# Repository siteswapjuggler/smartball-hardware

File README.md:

# Smartball project - hardware 

This repository contains the Smartball project hardware files: bom, schematics, board layout and 3D printed part.

## Open Source

All the technological development work made in the Smartball project is available under open source licenses. As we don't know yet about how we will deal with further development all of our hardwares will be published under Creative Commons BY-NC-SA and all of our softwares will be under GPL v3.

|Applying to|Licence|Logo|
|---|---|---|
|hardware|[Creatives Commons BY-NC-SA](http://creativecommons.org/licenses/by-nc-sa/4.0/)|[ ](http://creativecommons.org/licenses/by-nc-sa/4.0/)|
|software|[GPL v3](http://www.gnu.org/licenses/gpl.html)||

## Different boards

The project is an assembly of three boards: 2 led boards + 1 main board. It relies on the ESP-12F espressif breakout but could be used with ESP-12E or ESP-12F without any problem.

## Version history

v1.1 is the version product for the first prototypes and contains an minor error on USB Data Lines
v1.2 is the latest version, it correct the USB Data Lines error

## Linked repositories

This repository refers directly to its following siblings : 

- https://github.com/siteswapjuggler/smartball-firmware
- https://github.com/siteswapjuggler/smartball-externals
- https://github.com/siteswapjuggler/smartball-documents
- https://github.com/siteswapjuggler/smartball-imu

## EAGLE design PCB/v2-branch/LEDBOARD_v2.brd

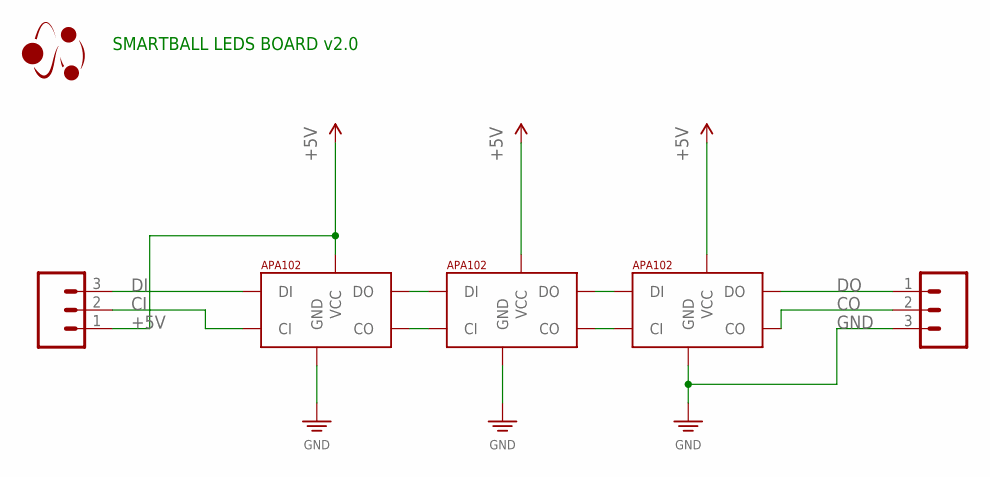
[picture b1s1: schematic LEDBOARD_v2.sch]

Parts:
L1, L2, L3: APA102; APA102_5050_SB
U$4: LOGO_SMARTBALL; SMARTBALL_LOGO
U$5, U$6: CONN_03_SMD_MALECONN03_SMD_MALE; CONN03_SMD_MALE

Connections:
+5V: L1.4 (VCC), L2.4 (VCC), L3.4 (VCC), U$5.1
CI: L1.2 (CI), L1.CI2 (CI), U$5.2
CO: L3.5 (CO), U$6.2
DI: L1.1 (DI), L1.DI2 (DI), U$5.3
DO: L3.6 (DO), U$6.1
GND: L1.3 (GND), L1.GND2 (GND), L2.3 (GND), L2.GND2 (GND), L3.3 (GND), L3.GND2 (GND), U$6.3
unnamed: L1.6 (DO), L2.1 (DI), L2.DI2 (DI)
unnamed: L1.5 (CO), L2.2 (CI), L2.CI2 (CI)
unnamed: L2.6 (DO), L3.1 (DI), L3.DI2 (DI)
unnamed: L2.5 (CO), L3.2 (CI), L3.CI2 (CI)

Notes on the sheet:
SMARTBALL LEDS BOARD v2.0

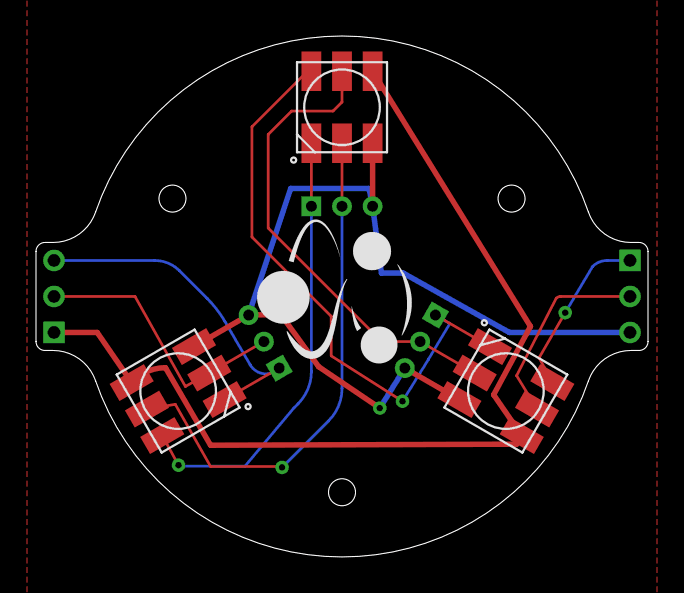
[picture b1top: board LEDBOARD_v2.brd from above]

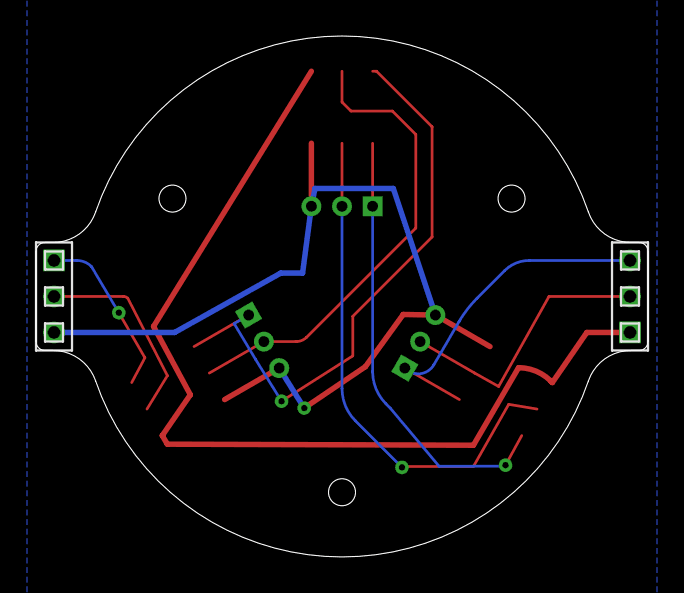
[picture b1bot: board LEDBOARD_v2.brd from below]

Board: 2 copper layers, 34.0 x 28.9 mm, 6 parts (2 on the bottom side), 10 nets.

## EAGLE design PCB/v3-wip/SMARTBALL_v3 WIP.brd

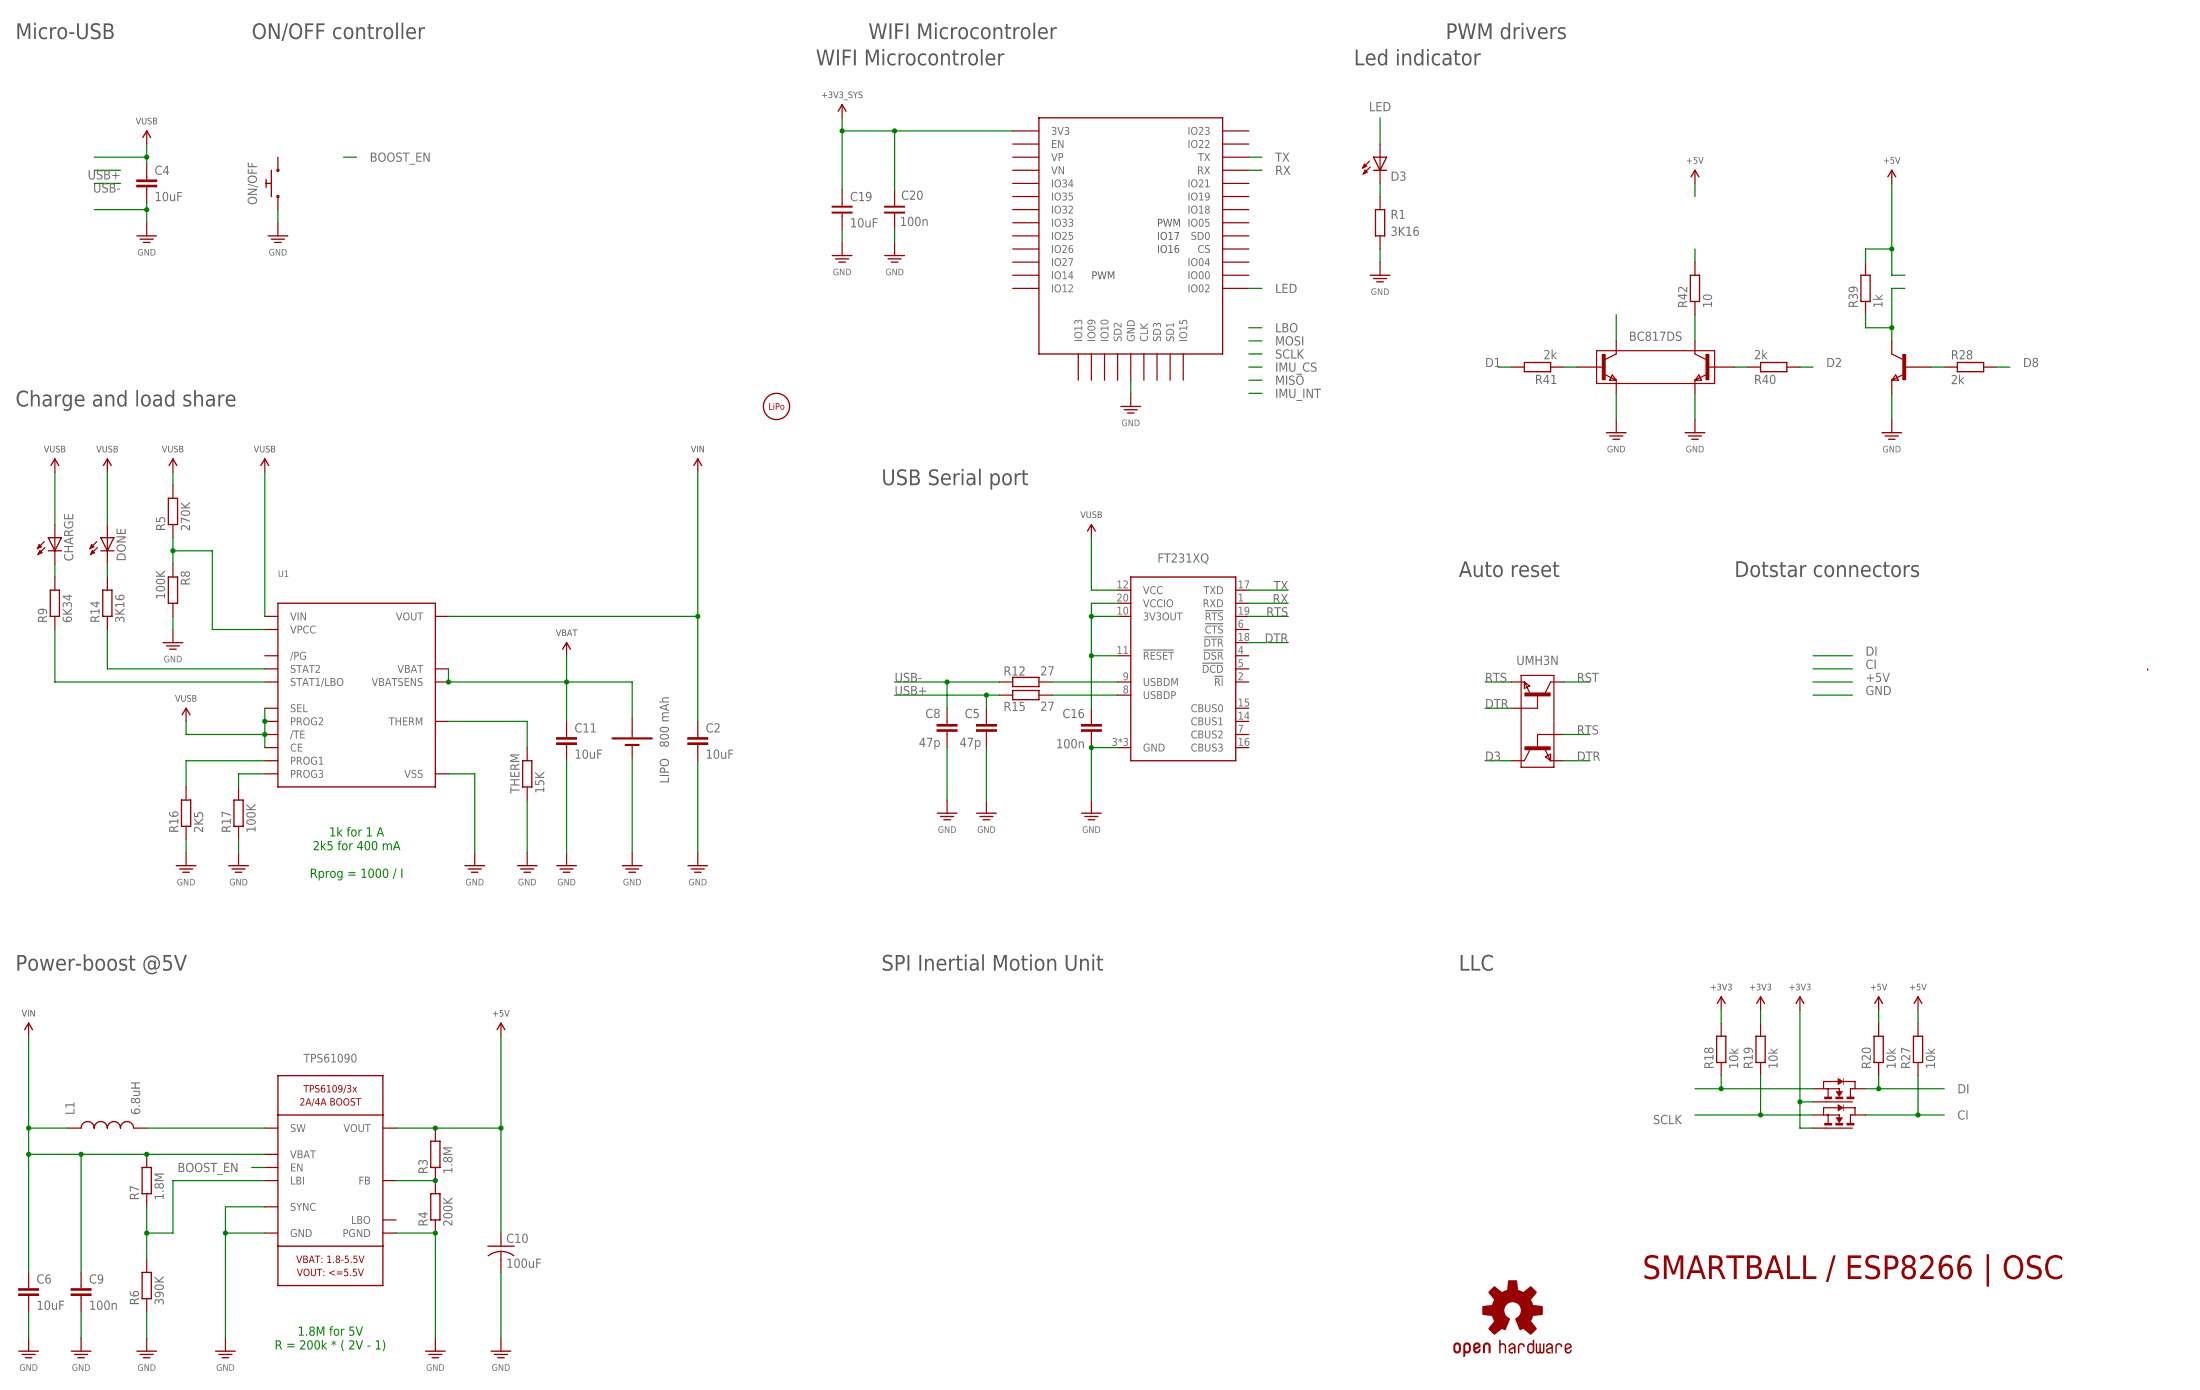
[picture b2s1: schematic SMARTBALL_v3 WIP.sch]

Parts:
BC817DS: SOT_BC817DS; SOT457R_PHILIPS
C2, C4, C6, C11, C19: 10uF; C0603
C5, C8: 47p; C0603
C9, C16, C20: 100n; C0603
C10: 100uF; C1210
CHARGE: LED_KINGBRIGHT_16X08
D3: Blue; LED_KINGBRIGHT_16X08
DONE: LED_KINGBRIGHT_16X08
FT231XQ: QFN_FT231X; QFN20
L1: 6.8uH; IND_ASPIAIG-S4035
LIPO: CONN_BATTERY; CONN_WIRES
LOGO1: LOGO_OSHWL; LOGO_OSHW
ON/OFF: BUT_KMR6
R1, R14: 3K16; R0402
R3, R7: 1.8M; R0402
R4: 200K; R0402
R5: 270K; R0402
R6: 390K; R0402
R8, R17: 100K; R0402
R9: 6K34; R0402
R12, R15: 27; R0402
R16: 2K5; R0402
R18, R19, R20, R27: 10k; R0402
R28, R40, R41: 2k; R0402
R39: 1k; R0402
R42: 10; R0402
THERM: 15K; R0402
TPS61090: TPS61090RSAR; QFN16
U1: QFN_MCP73871; QFN20
U6: ESP-MICRO32
U$22: SOT_2N7002PS; SOT363
U$28: SOT_SBC847AWT1G; SOT323
U$29: BATT_BODY
UMH3N: SOT_UMH3N; SOT363

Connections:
+3V3: R18.2, R19.2, U$22.2 (G1), U$22.5 (G2)
+3V3_SYS: C19.1, C20.1, U6.2 (3V3)
+5V: C10.1, R3.2, R20.2, R27.2, R39.2, TPS61090.1 (VOUT), TPS61090.15 (VOUT), TPS61090.16 (VOUT)
B1: BC817DS.5 (B2), R41.1
B2: BC817DS.2 (B1), R40.1
B3: R28.1, U$28.1 (B)
BOOST_EN: TPS61090.11 (EN)
C1: BC817DS.3 (C2)
C2: BC817DS.6 (C1), R42.1
C3: R39.1, U$28.3 (C)
CI: R27.1, U$22.3 (D2)
D1: R41.2
D2: R40.2
D3: UMH3N.3 (C2)
D8: R28.2
DI: R20.1, U$22.6 (D1)
DTR: FT231XQ.18 (!DTR), UMH3N.2 (B1), UMH3N.4 (E2)
FB: R3.1, R4.2, TPS61090.14 (FB)
GND: BC817DS.1 (E1), BC817DS.4 (E2), C2.2, C4.2, C5.2, C6.2, C8.2, C9.2, C10.2, C11.2, C16.2, C19.2, C20.2, FT231XQ.3 (GND), FT231XQ.13 (GND), FT231XQ.EXP (GND), LIPO.GND, ON/OFF.1, ON/OFF.4 (1), R1.1, R4.1, R6.1, R8.2, R16.1, R17.1, THERM.1, TPS61090.5 (PGND), TPS61090.6 (PGND), TPS61090.7 (PGND), TPS61090.10 (SYNC), TPS61090.13 (GND), TPS61090.PAD (PGND), U1.10 (VSS), U1.11 (VSS), U1.EXP (VSS), U6.1 (GND), U6.15 (GND), U6.38 (GND), U$28.2 (E)
LBI: R6.2, R7.1, TPS61090.9 (LBI)
LED: D3.1 (A), U6.24 (IO02)
LED1: DONE.2 (C), R14.2
LED2: CHARGE.2 (C), R9.2
LED3: D3.2 (C), R1.2
MOT: R42.2
PROG1: R16.2, U1.13 (PROG1)
PROG3: R17.2, U1.12 (PROG3)
RST: UMH3N.6 (C1)
RTS: FT231XQ.19 (!RTS), UMH3N.1 (E1), UMH3N.5 (B2)
RX: FT231XQ.1 (RXD), U6.34 (RX)
SCLK: R19.1, U$22.4 (S2)
STAT1: R9.1, U1.8 (STAT1/LBO)
STAT2: R14.1, U1.7 (STAT2)
SW: L1.2, TPS61090.3 (SW), TPS61090.4 (SW)
THERM: THERM.2, U1.5 (THERM)
TX: FT231XQ.17 (TXD), U6.35 (TX)
USB+: C5.1, R15.1
USB-: C8.1, R12.1
USBDM: FT231XQ.9 (USBDM), R12.2
USBDP: FT231XQ.8 (USBDP), R15.2
VBAT: C11.1, LIPO.VCC (VBAT), U1.14 (VBAT), U1.15 (VBAT), U1.16 (VBATSENS)
VCCIO1: C16.1, FT231XQ.10 (3V3OUT), FT231XQ.11 (!RESET), FT231XQ.20 (VCCIO)
VIN: C2.1, C6.1, C9.1, L1.1, R7.2, TPS61090.8 (VBAT), U1.1 (VOUT), U1.20 (VOUT)
VPCC: R5.1, R8.1, U1.2 (VPCC)
VUSB: C4.1, CHARGE.1 (A), DONE.1 (A), FT231XQ.12 (VCC), R5.2, U1.3 (SEL), U1.4 (PROG2), U1.9 (/TE), U1.17 (CE), U1.18 (VIN), U1.19 (VIN)
Y0: R18.1, U$22.1 (S1)

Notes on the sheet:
SMARTBALL / ESP8266 | OSC
1k for 1 A 2k5 for 400 mA Rprog = 1000 / I
Micro-USB
Charge and load share
ON/OFF controller
USB Serial port
WIFI Microcontroler
Auto reset
LLC
Dotstar connectors
PWM drivers
Power-boost @5V
SPI Inertial Motion Unit
800 mAh
1.8M for 5V R = 200k * ( 2V - 1)
Led indicator
IO17
IO16
PWM

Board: 2 copper layers, 50 parts (4 on the bottom side), 38 nets, no tracks yet.

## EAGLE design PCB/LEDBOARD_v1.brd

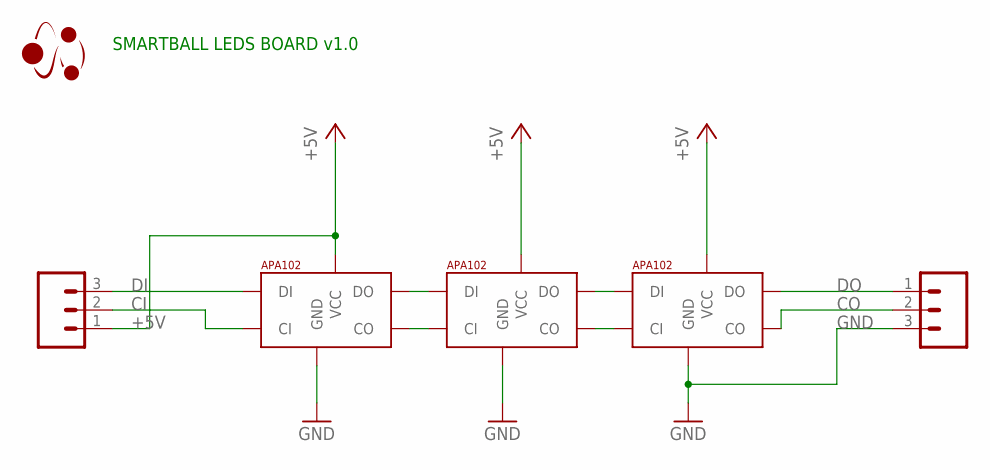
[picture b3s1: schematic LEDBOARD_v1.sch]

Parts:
U$1, U$2, U$3: APA102; APA102_5050_SB
U$4: LOGO_SMARTBALL; SMARTBALL_LOGO
U$5, U$6: CONN_03_SMDCONN03_SMD_MALE; CONN03_SMD_MALE

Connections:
+5V: U$1.VCC, U$2.VCC, U$3.VCC, U$5.1
CI: U$1.CI, U$1.CI2 (CI), U$5.2
CO: U$3.CO, U$6.2
DI: U$1.DI, U$1.DI2 (DI), U$5.3
DO: U$3.DO, U$6.1
GND: U$1.GND, U$1.GND2 (GND), U$2.GND, U$2.GND2 (GND), U$3.GND, U$3.GND2 (GND), U$6.3
unnamed: U$1.DO, U$2.DI, U$2.DI2 (DI)
unnamed: U$1.CO, U$2.CI, U$2.CI2 (CI)
unnamed: U$2.DO, U$3.DI, U$3.DI2 (DI)
unnamed: U$2.CO, U$3.CI, U$3.CI2 (CI)

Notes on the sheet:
SMARTBALL LEDS BOARD v1.0

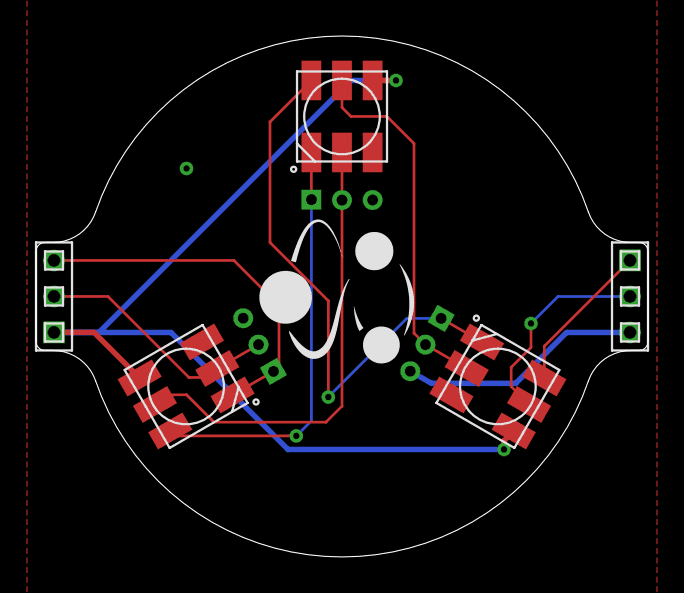
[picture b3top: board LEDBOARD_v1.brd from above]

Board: 2 copper layers, 34.0 x 28.9 mm, 6 parts (0 on the bottom side), 10 nets.

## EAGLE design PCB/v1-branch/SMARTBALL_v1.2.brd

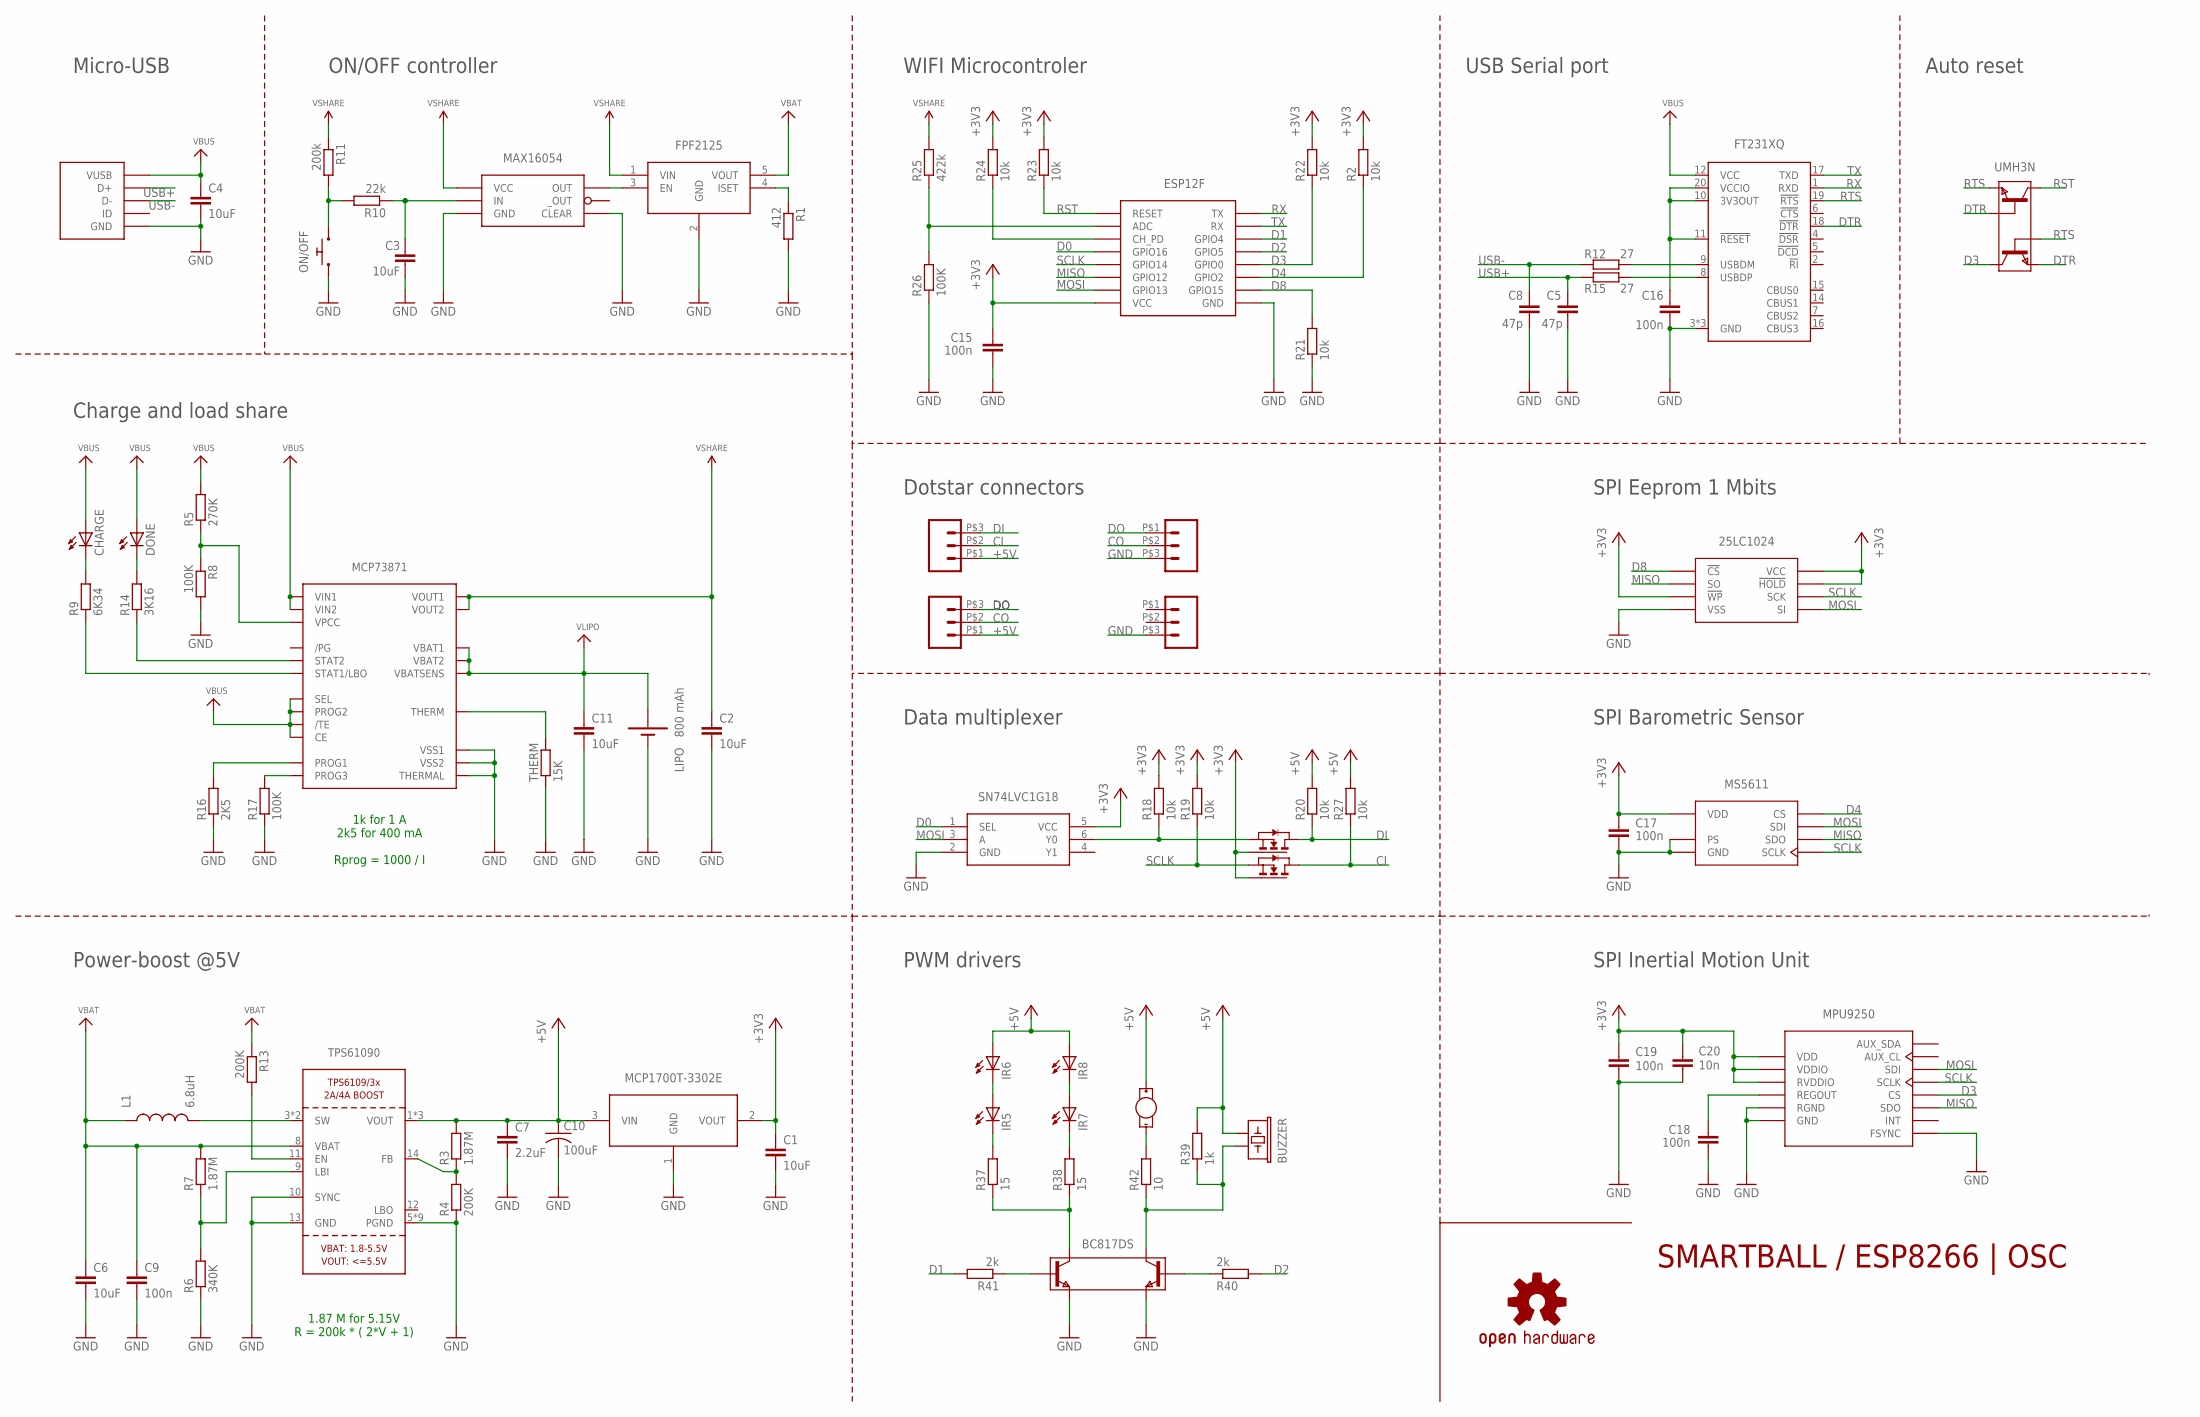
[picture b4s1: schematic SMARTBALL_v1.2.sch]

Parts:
BC817DS: BC817DS; SOT457R_PHILIPS
BUZZER: BUZZER_PKMCS0909E4000-R1
C1, C2, C3, C4, C6, C11: 10uF; C0603K
C5, C8: 47p; C0603K
C7: 2.2uF; C0603K
C9, C15, C16, C17, C18, C19: 100n; C0603K
C10: 100uF; C1210
C20: 10n; C0603K
CHARGE: KINGBRIGHT_16X08
DONE: KINGBRIGHT_16X08
ESP12F: ESP12
FT231XQ: FT231X; QFN20
IR5, IR6, IR7, IR8: LED-SFH4050; SFH4050
L1: 6.8uH; ASPIAIG-S4035
LIPO: BATTERY_CONNECTOR; MOTOR_CONNECTOR
LOGO1: OSHW-LOGOL; OSHW-LOGO-L
MCP73871: MCP73871; QFN20_4MM
MOTOR: MOTOR_CONNECTOR
ON/OFF: B3U-3000P-B
R1: 412; R0402
R2, R18, R19, R20, R21, R22, R23, R24, R27: 10k; R0402
R3, R7: 1.87M; R0402
R4, R13: 200K; R0402
R5: 270K; R0402
R6: 340K; R0402
R8, R17, R26: 100K; R0402
R9: 6K34; R0402
R10: 22k; R0402
R11: 200k; R0402
R12, R15: 27; R0402
R14: 3K16; R0402
R16: 2K5; R0402
R25: 422k; R0402
R37, R38: 15; R0402
R39: 1k; R0402
R40, R41: 2k; R0402
R42: 10; R0402
THERM: 15K; R0402
TPS61090: TPS61090RSAR; PVQFN-16
U$1: MOLEX-USB
U$2: FPF2125; SOT23-5
U$3: MCP1700T; SOT23-3
U$5, U$6, U$14, U$15: CONN_03_SMD; CONN03_SMD
U$12: MAX16054; TSOT23-6
U$16: 25LC1024DFN-S; DFN-S
U$17: MS5611; MS5611-QFN
U$20: SN74LVC1G18; DCK_R-PDSO-G6
U$21: MPU-9250QFN24G; QFN24G-0.4-3X3MM
U$22: 2N7002PS; SOT363_PHILIPS
UMH3N: UMH3N; SOT363_PHILIPS

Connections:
+3V3: C1.1, C15.1, C17.1, C19.1, C20.2, ESP12F.VCC, R2.2, R18.2, R19.2, R22.2, R23.2, R24.2, U$3.2 (VOUT), U$16.3 (!WP), U$16.7 (!HOLD), U$16.8 (VCC), U$17.P$1 (VDD), U$20.5 (VCC), U$21.1 (RVDDIO), U$21.8 (VDDIO), U$21.13 (VDD), U$22.2 (G1), U$22.5 (G2)
+5V: BUZZER.P$1 (1), C7.1, C10.1, IR6.P$1 (A), IR8.P$1 (A), MOTOR.+, R3.2, R20.2, R27.2, R39.2, TPS61090.1 (VOUT), TPS61090.15 (VOUT), TPS61090.16 (VOUT), U$3.3 (VIN), U$5.P$1 (1), U$15.P$1 (1)
CI: R27.1, U$5.P$2 (2), U$22.3 (D2)
CO: U$6.P$2 (2), U$15.P$2 (2)
D0: ESP12F.GPIO16, U$20.1 (SEL)
D1: ESP12F.GPIO4, R41.2
D2: ESP12F.GPIO5, R40.2
D3: ESP12F.GPIO0, R22.1, U$21.22 (CS), UMH3N.3 (C2)
D4: ESP12F.GPIO2, R2.1, U$17.P$4 (CS), U$17.P$5 (CS)
D8: ESP12F.GPIO15, R21.2, U$16.1 (!CS)
DI: R20.1, U$5.P$3 (3), U$22.6 (D1)
DO: U$6.P$1 (1), U$15.P$3 (3)
DTR: FT231XQ.18 (!DTR), UMH3N.2 (B1), UMH3N.4 (E2)
EN1: ESP12F.CH_PD, R24.1
ENABLE: R13.2, TPS61090.11 (EN)
GND: BC817DS.1 (E1), BC817DS.4 (E2), C1.2, C2.2, C3.2, C4.2, C5.2, C6.2, C7.2, C8.2, C9.2, C10.2, C11.2, C15.2, C16.2, C17.2, C18.2, C19.2, C20.1, ESP12F.GND, FT231XQ.3 (GND), FT231XQ.13 (GND), FT231XQ.EXP (GND), LIPO.-, MCP73871.P$10 (VSS1), MCP73871.P$11 (VSS2), MCP73871.P$21 (THERMAL), ON/OFF.P$1 (1), R1.2, R4.1, R6.1, R8.2, R16.1, R17.1, R21.1, R26.1, THERM.1, TPS61090.5 (PGND), TPS61090.6 (PGND), TPS61090.7 (PGND), TPS61090.10 (SYNC), TPS61090.13 (GND), TPS61090.P$18 (PGND), TPS61090.P$19 (PGND), TPS61090.P$20 (PGND), TPS61090.P$21 (PGND), TPS61090.P$22 (PGND), TPS61090.THERMAL (PGND), U$1.GND, U$1.P$1 (GND), U$1.P$11 (GND), U$1.SHELL1 (GND), U$1.SHELL2 (GND), U$1.SHELL5 (GND), U$1.SHELL6 (GND), U$2.2 (GND), U$3.1 (GND), U$6.P$3 (3), U$12.CLEAR, U$12.GND, U$14.P$3 (3), U$16.4 (VSS), U$17.P$2 (PS), U$17.P$3 (GND), U$20.2 (GND), U$21.11 (FSYNC), U$21.18 (GND), U$21.20 (RGND)
MISO: ESP12F.GPIO12, U$16.2 (SO), U$17.P$6 (SDO), U$21.9 (SDO)
MOSI: ESP12F.GPIO13, U$16.5 (SI), U$17.P$7 (SDI), U$20.3 (A), U$21.24 (SDI)
unnamed: U$2.3 (EN), U$12.OUT
unnamed: R1.1, U$2.4 (ISET)
unnamed: MCP73871.P$2 (VPCC), R5.1, R8.1
unnamed: MCP73871.P$13 (PROG1), R16.2
unnamed: FT231XQ.9 (USBDM), R12.2
unnamed: FT231XQ.8 (USBDP), R15.2
unnamed: ON/OFF.P$2 (2), R10.2, R11.2
unnamed: C3.1, R10.1, U$12.IN
unnamed: R18.1, U$20.6 (Y0), U$22.1 (S1)
unnamed: ESP12F.ADC, R25.1, R26.2
unnamed: L1.P$2 (2), TPS61090.3 (SW), TPS61090.4 (SW)
unnamed: R6.2, R7.1, TPS61090.9 (LBI)
unnamed: R3.1, R4.2, TPS61090.14 (FB)
unnamed: MCP73871.P$7 (STAT2), R14.1
unnamed: MCP73871.P$8 (STAT1/LBO), R9.1
unnamed: MCP73871.P$5 (THERM), THERM.2
unnamed: DONE.CATHODE (C), R14.2
unnamed: CHARGE.CATHODE (C), R9.2
unnamed: MCP73871.P$12 (PROG3), R17.2
unnamed: IR5.P$2 (C), R37.2
unnamed: IR5.P$1 (A), IR6.P$2 (C)
unnamed: BC817DS.3 (C2), R37.1, R38.1
unnamed: IR7.P$2 (C), R38.2
unnamed: IR7.P$1 (A), IR8.P$2 (C)
unnamed: BC817DS.6 (C1), BUZZER.P$2 (2), R39.1, R42.1
unnamed: MOTOR.-, R42.2
unnamed: BC817DS.5 (B2), R41.1
unnamed: BC817DS.2 (B1), R40.1
REGOUT1: C18.1, U$21.10 (REGOUT)
RST: ESP12F.RESET, R23.1, UMH3N.6 (C1)
RTS: FT231XQ.19 (!RTS), UMH3N.1 (E1), UMH3N.5 (B2)
RX: ESP12F.TX, FT231XQ.1 (RXD)
SCLK: ESP12F.GPIO14, R19.1, U$16.6 (SCK), U$17.P$8 (SCLK), U$21.23 (SCLK), U$22.4 (S2)
TX: ESP12F.RX, FT231XQ.17 (TXD)
USB+: C5.1, R15.1, U$1.D+
USB-: C8.1, R12.1, U$1.D-
VBAT: C6.1, C9.1, L1.P$1 (1), R7.2, R13.1, TPS61090.8 (VBAT), U$2.5 (VOUT)
VBUS: C4.1, CHARGE.ANODE (A), DONE.ANODE (A), FT231XQ.12 (VCC), MCP73871.P$3 (SEL), MCP73871.P$4 (PROG2), MCP73871.P$9 (/TE), MCP73871.P$17 (CE), MCP73871.P$18 (VIN1), MCP73871.P$19 (VIN2), R5.2, U$1.VUSB
VCCIO1: C16.1, FT231XQ.10 (3V3OUT), FT231XQ.11 (!RESET), FT231XQ.20 (VCCIO)
VLIPO: C11.1, LIPO.+, MCP73871.P$14 (VBAT1), MCP73871.P$15 (VBAT2), MCP73871.P$16 (VBATSENS)
VSHARE: C2.1, MCP73871.P$1 (VOUT1), MCP73871.P$20 (VOUT2), R11.1, R25.2, U$2.1 (VIN), U$12.VCC

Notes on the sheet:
SMARTBALL / ESP8266 | OSC
MCP1700T-3302E
1k for 1 A 2k5 for 400 mA Rprog = 1000 / I
Micro-USB
Charge and load share
ON/OFF controller
USB Serial port
WIFI Microcontroler
Auto reset
Data multiplexer
Dotstar connectors
PWM drivers
Power-boost @5V
SPI Inertial Motion Unit
SPI Eeprom 1 Mbits
SPI Barometric Sensor
800 mAh
MAX16054
FPF2125
SN74LVC1G18
1.87 M for 5.15V R = 200k * ( 2*V + 1)

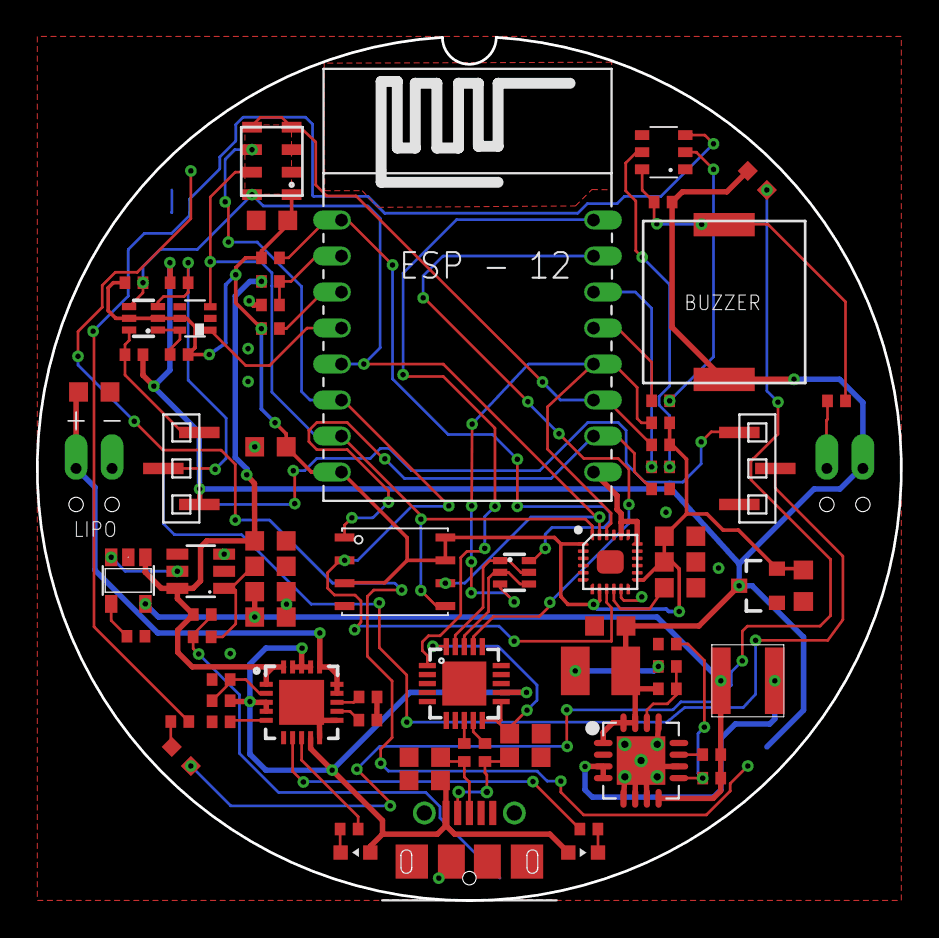
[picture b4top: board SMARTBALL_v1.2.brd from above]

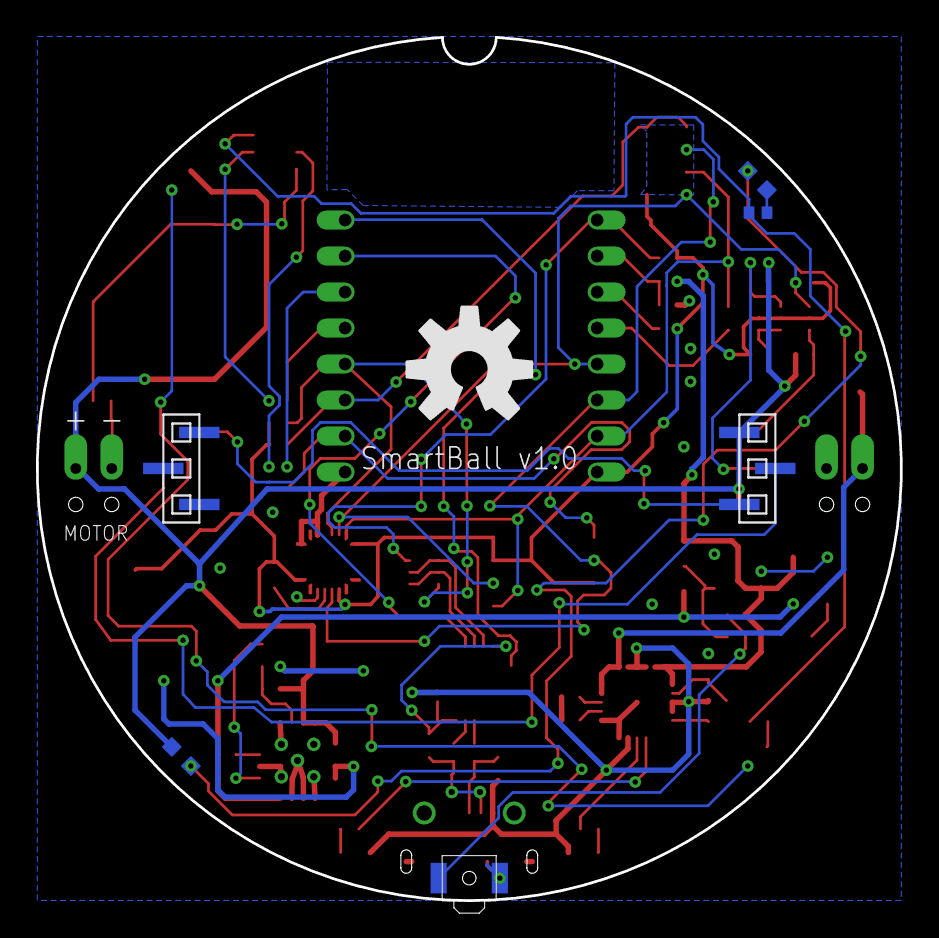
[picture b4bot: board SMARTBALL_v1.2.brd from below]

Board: 2 copper layers, 48.0 x 48.0 mm, 82 parts (8 on the bottom side), 59 nets.

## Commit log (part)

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2019-08-19 PCB support v5
2019-08-19 schematic update
2022-10-16 loads of change since v1
2022-10-16 folder by version

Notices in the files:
parts and their libraries:
microbuilder: This work is placed in the public domain, and may be freely used for commercial and non-commercial work with the following conditions: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
SparkFun-Aesthetics: Licensing: Creative Commons ShareAlike 4.0 International - https://creativecommons.org/licenses/by-sa/4.0
